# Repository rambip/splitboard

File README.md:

# Splitboard

This is the ressources we use to create our split, type matrix, bluetooth, mecanical custom keyboard.

Still in construction !

We used a lot of different technologies (solidworks for example), so you probably will not be able to recreate exactly the same keyboard.

But we added ressources you can use if you want to make your own !

## Description

pcb + 3d-printed box + aluminium plate + brown switches + adafruit feather 32u4

### Design goals:

- comfortable
	Ergonomics was the first goal of this model.
	Even if we had to make tradeoffs, the first choices (2 parts, mechanical switches, design of a new layout) were made to increase comfort.

- portable
	It is a tiny keyboard: 46 keys, measure less than 24x12 cm
	Every key has to be reachable without moving your hands at all !

- robust
	I didn't broke it yet !

- usb and bluetooth
        You can use it with any computer (mac or pc) and any modern smartphone

Our keyboard supports usb and bluetooth (BLE) communication with the *hid* specification.

## Content:

 - board design, with all components (kicad and gerber files) → `pcb`
 - ready to print STL files → `printing`
 - 3d modeling of the entire keyboard (solidworks and .step) → `3d`
 - arduino code for card → `code`

## 3d structure:

- box

- pcb

- plate

- switches

We chose the [cherry mx brown](https://www.cherrymx.de/en/mx-original/mx-brown.html).

> Pro tip: Before buying, try to find a second-hand broken keyboard somewhere !

## PCB and electronics:

We used the [adafruit 32u4](https://learn.adafruit.com/adafruit-feather-32u4-bluefruit-le/overview).

Go check out their [github account](https://github.com/adafruit), they have a lot of cool stuff !

## Software:

### Arduino

you can test our sketches if you have a 32u4 adafruit feather.

linux with arduino-cli:

First, make sure you are part of the `uucp` group.
If not, use the command `gpasswd -a $USER uucp`

`arduino-cli core install adafruit:avr`

find the board connected to usb (look at the *Port* path):
`arduino-cli board list` 

`arduino-cli board attach adafruit:avr:feather32u4`
`arduino-cli compile`
`arduino-cli upload`

### Ressources:
https://wiki.osdev.org/USB_Human_Interface_Devices

## TODO:

- [ ] convert all 3d modeling to .step
- [ ] add links to documentation

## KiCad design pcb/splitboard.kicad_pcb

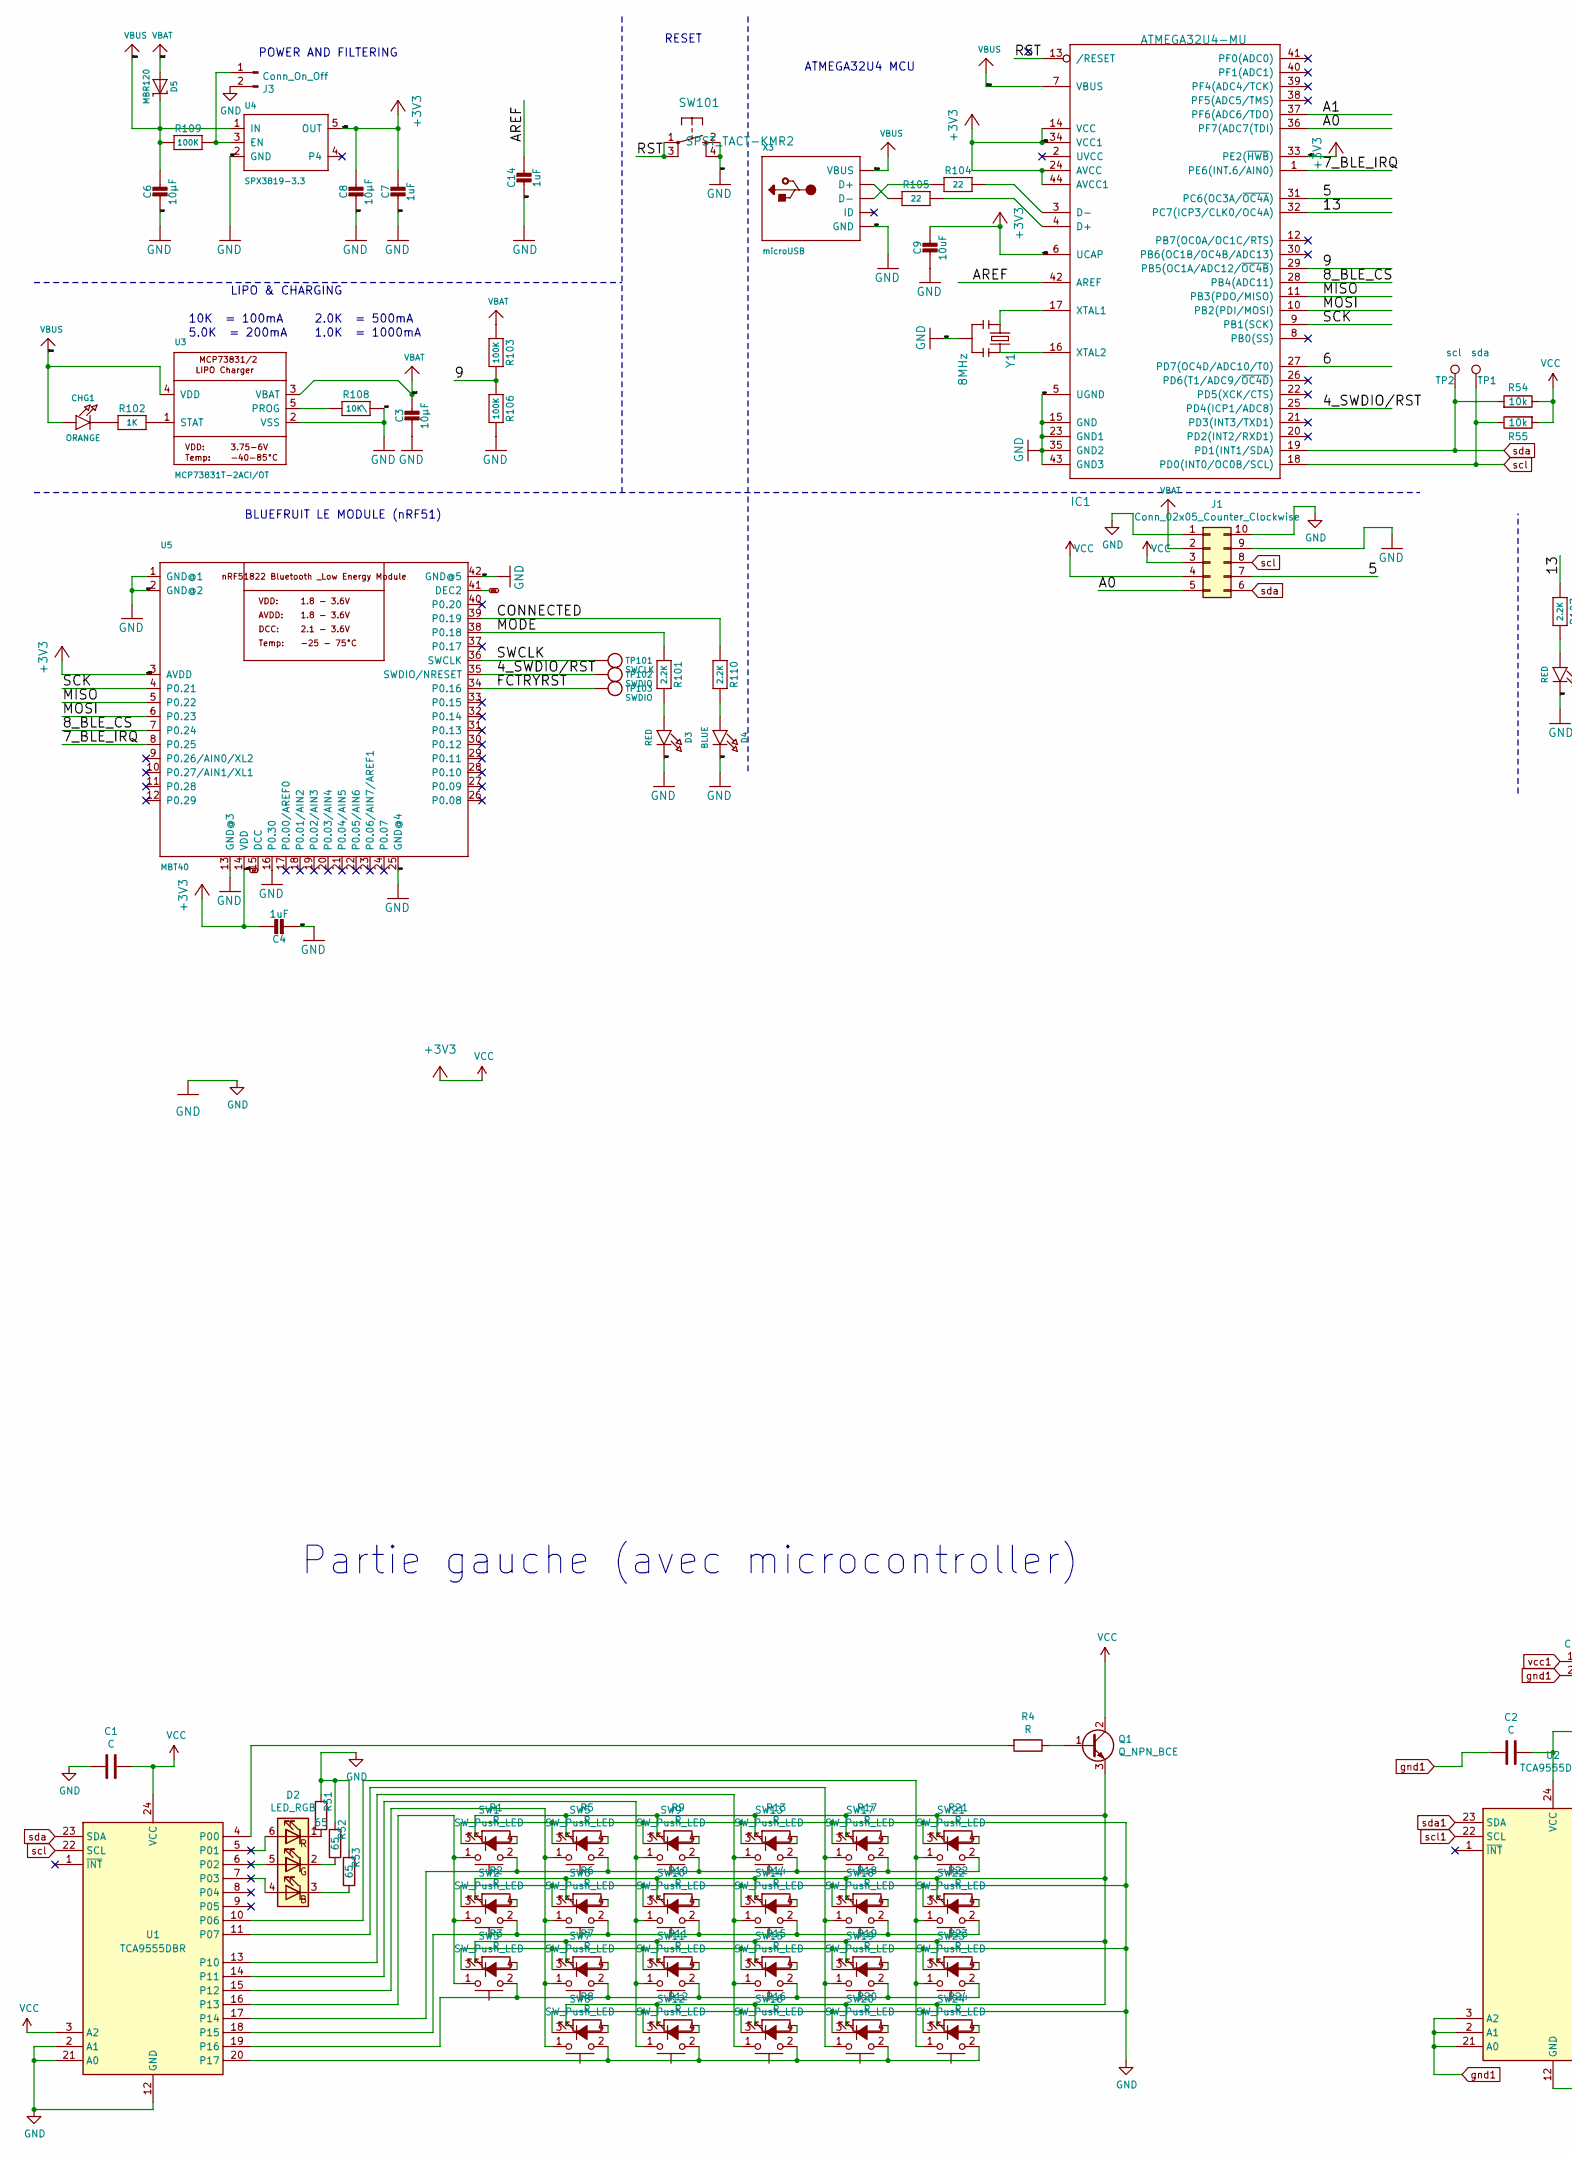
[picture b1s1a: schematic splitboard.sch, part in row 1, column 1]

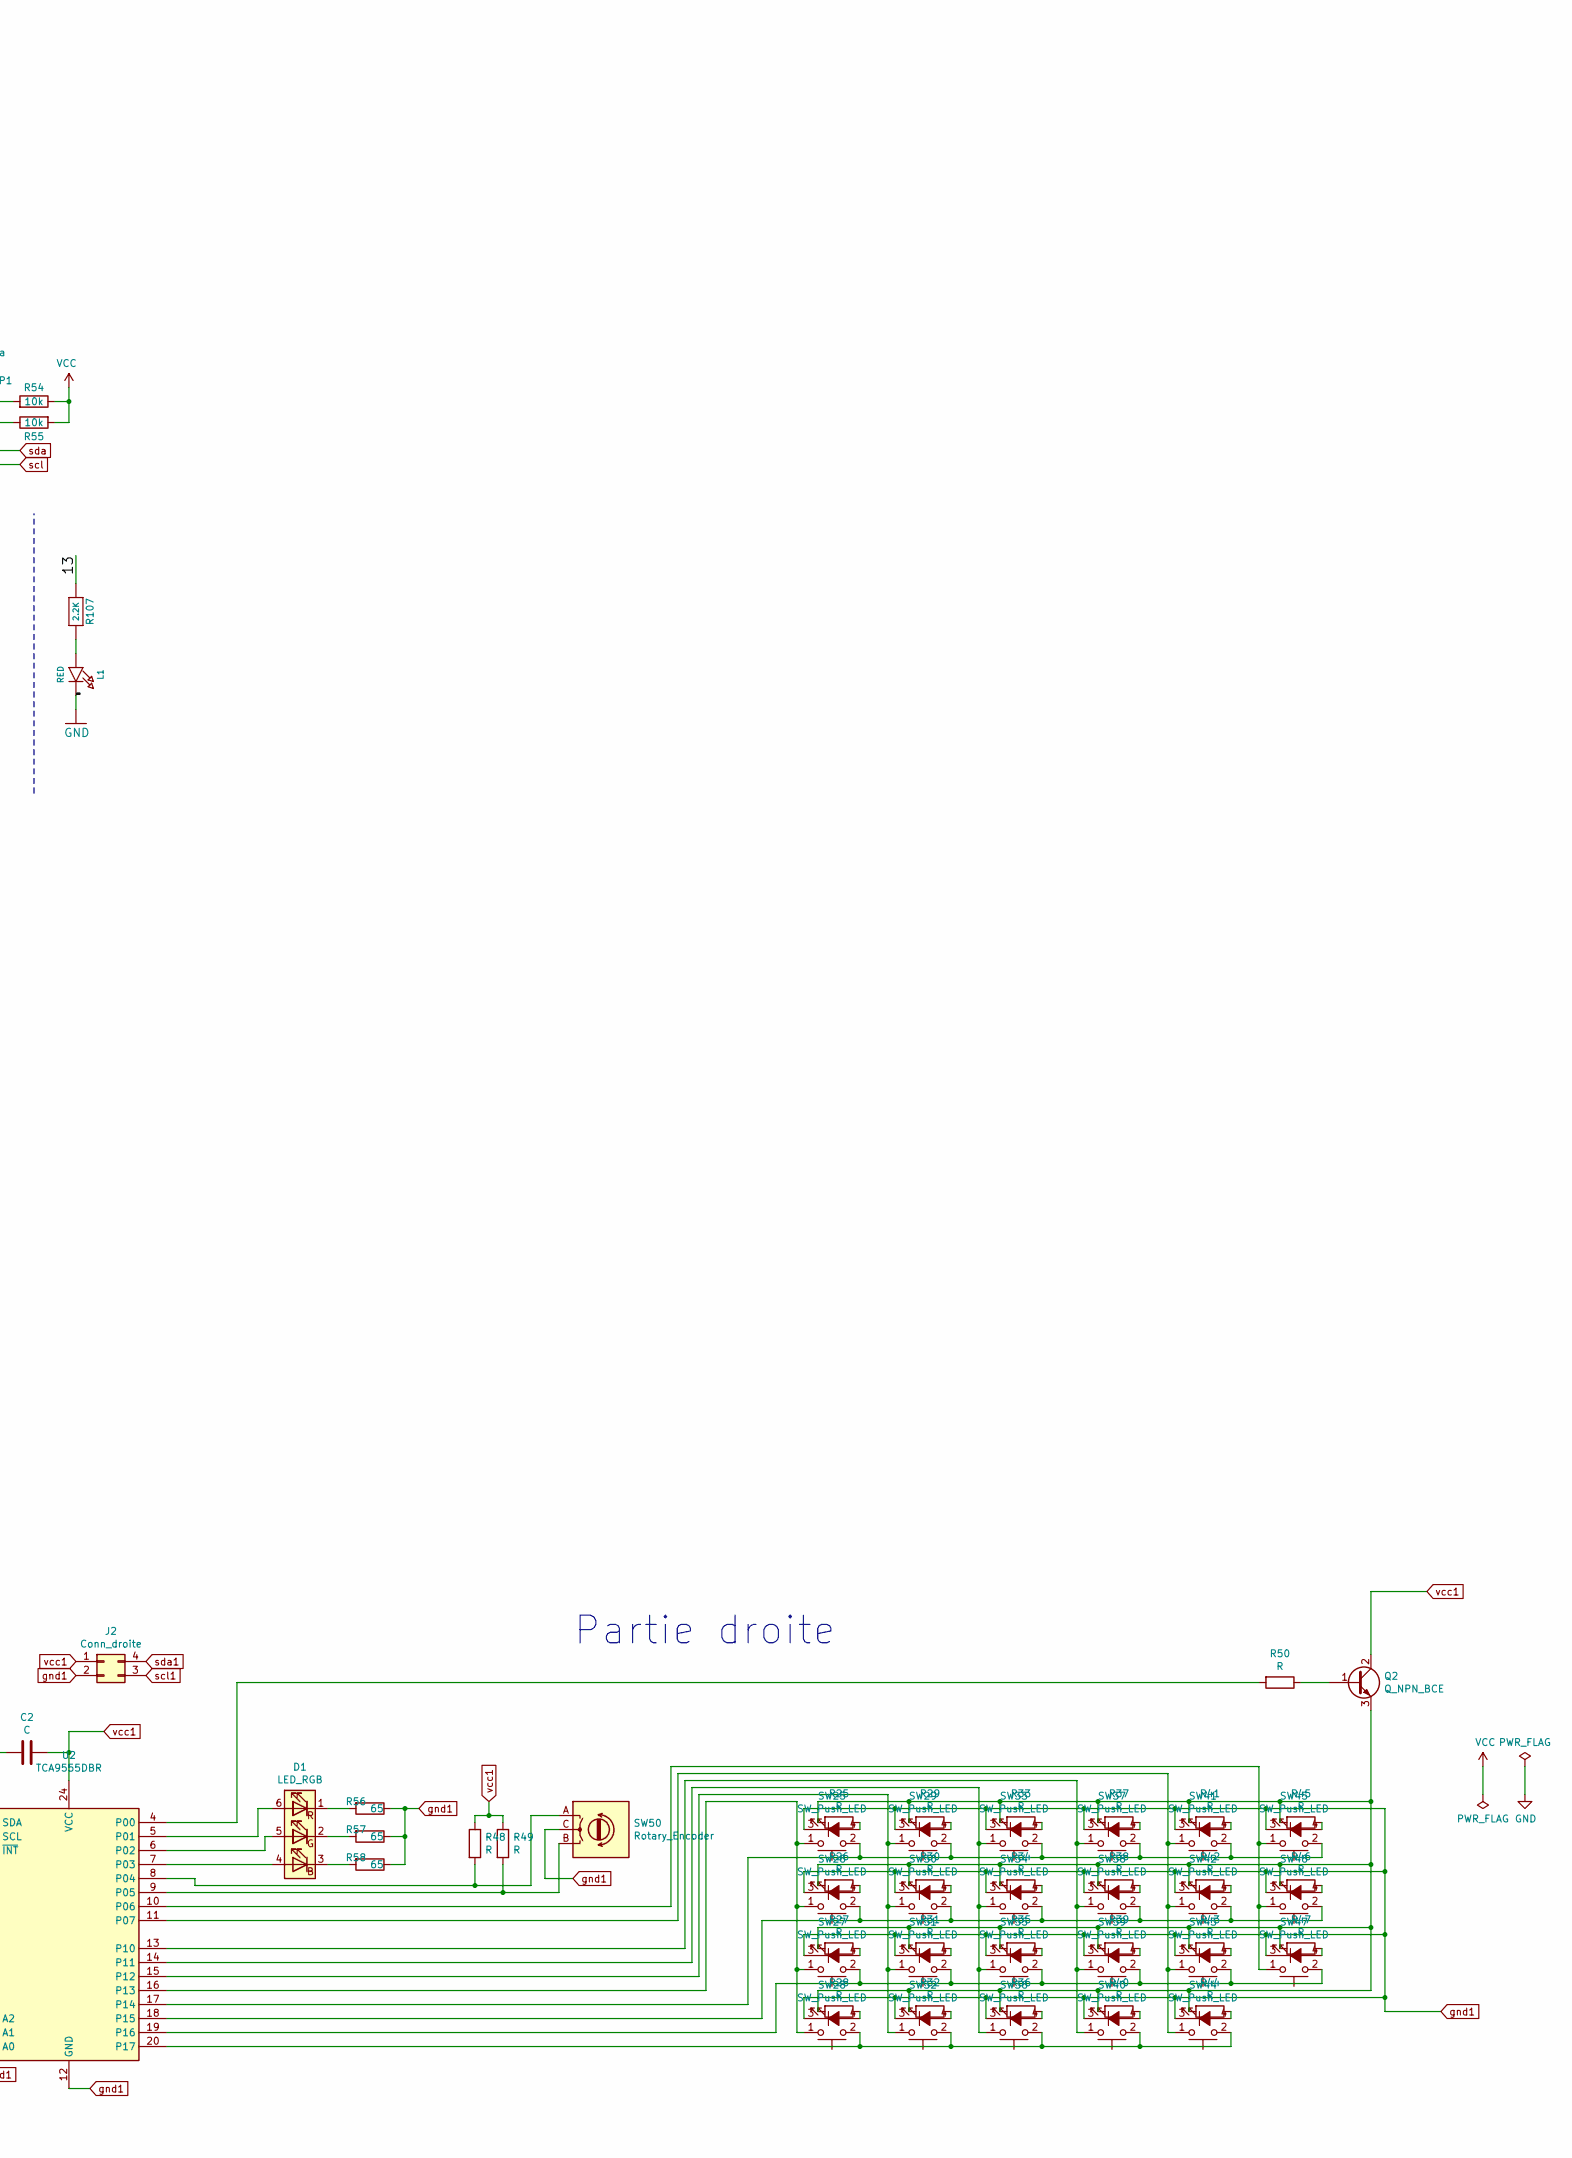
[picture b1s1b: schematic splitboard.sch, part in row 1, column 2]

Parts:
C1, C2: C; C_0603_HandSoldering
C3, C6, C8: 10µF; 0805-NO
C4, C7, C14: 1uF; 0603-NO
C9: 10uF; _0805MP
CHG1: ORANGE; CHIPLED_0805_NOOUTLINE
D1, D2: LED_RGB; LED_WS2812_PLCC6_5.0x5.0mm_P1.6mm
D3: RED; CHIPLED_0805_NOOUTLINE
D4: BLUE; CHIPLED_0805_NOOUTLINE
D5: MBR120; SOD-123
IC1: ATMEGA32U4-MU; TQFN44_7MM
J1: Conn_02x05_Counter_Clockwise; Pin_Header_Straight_2x05_Pitch2.54mm
J2: Conn_droite; PinHeader_2x02_P2.54mm_Vertical
J3: Conn_On_Off; PinHeader_1x02_P2.54mm_Vertical
L1: RED; CHIPLED_0805_NOOUTLINE
Q1, Q2: Q_NPN_BCE; SOT-23
R1, R2, R3, R4, R5, R6, R7, R8, R9, R10, R11, R12, R13, R14, R15, R16, R17, R18, R19, R20, R21, R22, R23, R24, R25, R26, R27, R28, R29, R30, R31, R32, R33, R34, R35, R36, R37, R38, R39, R40, R41, R42, R43, R44, R45, R46, R47, R48, R49, R50: R; R_0603_HandSoldering
R51, R52, R53: 65; R_0201_0603Metric_Pad0.64x0.40mm_HandSolder
R54, R55: 10k; R_0603_HandSoldering
R56, R57, R58: 65; R_0603_HandSoldering
R101, R107, R110: 2.2K; 0603-NO
R102: 1K; 0603-NO
R103, R106, R109: 100K; 0603-NO
R104, R105: 22; 0603-NO
R108: 10K\\; 0603-NO
SW1, SW2, SW3, SW5, SW6, SW7, SW8, SW9, SW10, SW11, SW12, SW13, SW14, SW15, SW16, SW17, SW18, SW19, SW20, SW21, SW22, SW23, SW24, SW25, SW26, SW27, SW28, SW29, SW30, SW31, SW32, SW33, SW34, SW35, SW36, SW37, SW38, SW39, SW40, SW41, SW42, SW43, SW44, SW45, SW46, SW47: SW_Push_LED; SW_Cherry_MX_1.00u_Plate_led
SW50: Rotary_Encoder; RotaryEncoder_Alps_EC12E_Vertical_H20mm
SW101: SPST_TACT-KMR2; KMR2
TP1: sda; TestPoint_Pad_D1.0mm
TP2: scl; TestPoint_Pad_D1.0mm
TP101: SWCLK; PAD-1.5X2.0
TP102, TP103: SWDIO; PAD-1.5X2.0
U1, U2: TCA9555DBR; SSOP-24_5.3x8.2mm_P0.65mm
U3: MCP73831T-2ACI/OT; SOT23-5
U4: SPX3819-3.3; SOT23-5
U5: MBT40; BLE_MODULE_RAYTAC_MDBT40
X3: microUSB; 4UCONN_20329_V2
Y1: 8MHz; RESONATOR-SMD

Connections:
+3V3: C1.1, C4.1, C7.1, C8.1, C9.1, IC1.6 (UCAP), IC1.14 (VCC), IC1.24 (AVCC), IC1.33 (PE2(~HWB)), IC1.34 (VCC1), IC1.44 (AVCC1), J1.3, J1.4, Q1.2 (C), R54.1, R55.2, U1.3 (A2), U1.24 (VCC), U4.5 (OUT), U5.3 (AVDD), U5.14 (VDD)
/4_SWDIO/RST: IC1.25 (PD4(ICP1/ADC8)), TP102.P$1, U5.35 (SWDIO/NRESET)
/5: IC1.31 (PC6(OC3A/~OC4A)), J1.7
/6: IC1.27 (PD7(OC4D/ADC10/T0))
/7_BLE_IRQ: IC1.1 (PE6(INT.6/AIN0)), U5.8 (P0.25)
/8_BLE_CS: IC1.28 (PB4(ADC11)), U5.7 (P0.24)
/9: IC1.29 (PB5(OC1A/ADC12/~OC4B)), R103.2, R106.1
/13: IC1.32 (PC7(ICP3/CLK0/OC4A)), R107.1
/A0: IC1.36 (PF7(ADC7(TDI)), J1.5
/A1: IC1.37 (PF6(ADC6/TDO))
/AREF: C14.1, IC1.42 (AREF)
/CONNECTED: R110.1, U5.39 (P0.19)
/FCTRYRST: TP103.P$1, U5.34 (P0.16)
/MISO: IC1.11 (PB3(PDO/MISO)), U5.5 (P0.22)
/MODE: R101.1, U5.38 (P0.18)
/MOSI: IC1.10 (PB2(PDI/MOSI)), U5.6 (P0.23)
/RST: IC1.13 (/RESET), SW101.1, SW101.3 (P1)
/SCK: IC1.9 (PB1(SCK)), U5.4 (P0.21)
/SWCLK: TP101.P$1, U5.36 (SWCLK)
DCC: U5.15 (DCC)
DEC2: U5.41 (DEC2)
GND: C1.2, C3.2, C4.2, C6.2, C7.2, C8.2, C9.2, C14.2, D3.C, D4.C, IC1.5 (UGND), IC1.15 (GND), IC1.23 (GND1), IC1.35 (GND2), IC1.43 (GND3), J1.1, J1.9, J1.10, J3.2, L1.C, R51.2, R52.2, R53.2, R106.2, R108.2, SW1.3 (K), SW2.3 (K), SW3.3 (K), SW5.3 (K), SW6.3 (K), SW7.3 (K), SW8.3 (K), SW9.3 (K), SW10.3 (K), SW11.3 (K), SW12.3 (K), SW13.3 (K), SW14.3 (K), SW15.3 (K), SW16.3 (K), SW17.3 (K), SW18.3 (K), SW19.3 (K), SW20.3 (K), SW21.3 (K), SW22.3 (K), SW23.3 (K), SW24.3 (K), SW101.2 (S), SW101.4 (S1), U1.2 (A1), U1.12 (GND), U1.21 (A0), U3.2 (VSS), U4.2 (GND), U5.1 (GND@1), U5.2 (GND@2), U5.13 (GND@3), U5.16 (P0.30), U5.25 (GND@4), U5.42 (GND@5), X3.BASE@1 (GND), X3.BASE@2 (GND), X3.GND, X3.SPRT@1 (GND), X3.SPRT@2 (GND), X3.SPRT@3 (GND), X3.SPRT@4 (GND), Y1.2
unnamed: CHG1.C, R102.1
unnamed: D1.1 (RK), R56.2
unnamed: D1.2 (GK), R57.2
unnamed: D1.3 (BK), R58.2
unnamed: D1.4 (BA), U2.7 (P03)
unnamed: D1.5 (GA), U2.6 (P02)
unnamed: D1.6 (RA), U2.5 (P01)
unnamed: D2.1 (RK), R51.1
unnamed: D2.2 (GK), R52.1
unnamed: D2.3 (BK), R53.1
unnamed: D2.4 (BA), U1.7 (P03)
unnamed: D2.5 (GA), U1.6 (P02)
unnamed: D2.6 (RA), U1.5 (P01)
unnamed: D3.A, R101.2
unnamed: D4.A, R110.2
unnamed: IC1.3 (D-), R104.2
unnamed: IC1.4 (D+), R105.2
unnamed: IC1.16 (XTAL2), Y1.3
unnamed: IC1.17 (XTAL1), Y1.1
unnamed: J3.1, R109.2, U4.3 (EN)
unnamed: L1.A, R107.2
unnamed: Q1.1 (B), R4.1
unnamed: Q1.3 (E), R1.2, R2.2, R3.2, R5.2, R6.2, R7.2, R8.2, R9.2, R10.2, R11.2, R12.2, R13.2, R14.2, R15.2, R16.2, R17.2, R18.2, R19.2, R20.2, R21.2, R22.2, R23.2, R24.2
unnamed: Q2.1 (B), R50.1
unnamed: Q2.3 (E), R25.2, R26.2, R27.2, R28.2, R29.2, R30.2, R31.2, R32.2, R33.2, R34.2, R35.2, R36.2, R37.2, R38.2, R39.2, R40.2, R41.2, R42.2, R43.2, R44.2, R45.2, R46.2, R47.2
unnamed: R1.1, SW1.4 (A)
unnamed: R2.1, SW2.4 (A)
unnamed: R3.1, SW3.4 (A)
unnamed: R4.2, U1.4 (P00)
unnamed: R5.1, SW5.4 (A)
unnamed: R6.1, SW6.4 (A)
unnamed: R7.1, SW7.4 (A)
unnamed: R8.1, SW8.4 (A)
unnamed: R9.1, SW9.4 (A)
unnamed: R10.1, SW10.4 (A)
unnamed: R11.1, SW11.4 (A)
unnamed: R12.1, SW12.4 (A)
unnamed: R13.1, SW13.4 (A)
unnamed: R14.1, SW14.4 (A)
unnamed: R15.1, SW15.4 (A)
unnamed: R16.1, SW16.4 (A)
unnamed: R17.1, SW17.4 (A)
unnamed: R18.1, SW18.4 (A)
unnamed: R19.1, SW19.4 (A)
unnamed: R20.1, SW20.4 (A)
unnamed: R21.1, SW21.4 (A)
unnamed: R22.1, SW22.4 (A)
unnamed: R23.1, SW23.4 (A)
unnamed: R24.1, SW24.4 (A)
unnamed: R25.1, SW25.4 (A)
unnamed: R26.1, SW26.4 (A)
unnamed: R27.1, SW27.4 (A)
unnamed: R28.1, SW28.4 (A)
unnamed: R29.1, SW29.4 (A)
unnamed: R30.1, SW30.4 (A)
unnamed: R31.1, SW31.4 (A)
unnamed: R32.1, SW32.4 (A)
unnamed: R33.1, SW33.4 (A)
unnamed: R34.1, SW34.4 (A)
unnamed: R35.1, SW35.4 (A)
unnamed: R36.1, SW36.4 (A)
unnamed: R37.1, SW37.4 (A)
unnamed: R38.1, SW38.4 (A)
unnamed: R39.1, SW39.4 (A)
unnamed: R40.1, SW40.4 (A)
unnamed: R41.1, SW41.4 (A)
unnamed: R42.1, SW42.4 (A)
unnamed: R43.1, SW43.4 (A)
unnamed: R44.1, SW44.4 (A)
unnamed: R45.1, SW45.4 (A)
unnamed: R46.1, SW46.4 (A)
unnamed: R47.1, SW47.4 (A)
unnamed: R48.2, SW50.A, U2.8 (P04)
unnamed: R49.2, SW50.B, U2.9 (P05)
unnamed: R50.2, U2.4 (P00)
unnamed: R102.2, U3.1 (STAT)
unnamed: R104.1, X3.D-
unnamed: R105.1, X3.D+
unnamed: R108.1, U3.5 (PROG)
unnamed: SW1.1, SW2.1, SW3.1, U1.16 (P13)
unnamed: SW1.2, SW5.2, SW9.2, SW13.2, SW17.2, SW21.2, U1.17 (P14)
unnamed: SW5.1, SW6.1, SW7.1, SW8.1, U1.15 (P12)
unnamed: SW9.1, SW10.1, SW11.1, SW12.1, U1.14 (P11)
unnamed: SW2.2, SW6.2, SW10.2, SW14.2, SW18.2, SW22.2, U1.18 (P15)
unnamed: SW3.2, SW7.2, SW11.2, SW15.2, SW19.2, SW23.2, U1.19 (P16)
unnamed: SW8.2, SW12.2, SW16.2, SW20.2, SW24.2, U1.20 (P17)
unnamed: SW13.1, SW14.1, SW15.1, SW16.1, U1.13 (P10)
unnamed: SW17.1, SW18.1, SW19.1, SW20.1, U1.11 (P07)
unnamed: SW21.1, SW22.1, SW23.1, SW24.1, U1.10 (P06)
unnamed: SW25.1, SW26.1, SW27.1, SW28.1, U2.16 (P13)
unnamed: SW25.2, SW29.2, SW33.2, SW37.2, SW41.2, SW45.2, U2.17 (P14)
unnamed: SW26.2, SW30.2, SW34.2, SW38.2, SW42.2, SW46.2, U2.18 (P15)
unnamed: SW27.2, SW31.2, SW35.2, SW39.2, SW43.2, SW47.2, U2.19 (P16)
unnamed: SW28.2, SW32.2, SW36.2, SW40.2, SW44.2, U2.20 (P17)
unnamed: SW29.1, SW30.1, SW31.1, SW32.1, U2.15 (P12)
unnamed: SW33.1, SW34.1, SW35.1, SW36.1, U2.14 (P11)
unnamed: SW37.1, SW38.1, SW39.1, SW40.1, U2.13 (P10)
unnamed: SW41.1, SW42.1, SW43.1, SW44.1, U2.11 (P07)
unnamed: SW45.1, SW46.1, SW47.1, U2.10 (P06)
VBAT: C3.1, D5.A, J1.2, R103.1, U3.3 (VBAT)
VBUS: C6.1, CHG1.A, D5.C, IC1.7 (VBUS), R109.1, U3.4 (VDD), U4.1 (IN), X3.VBUS
gnd1: C2.2, J2.2, R56.1, R57.1, R58.1, SW25.3 (K), SW26.3 (K), SW27.3 (K), SW28.3 (K), SW29.3 (K), SW30.3 (K), SW31.3 (K), SW32.3 (K), SW33.3 (K), SW34.3 (K), SW35.3 (K), SW36.3 (K), SW37.3 (K), SW38.3 (K), SW39.3 (K), SW40.3 (K), SW41.3 (K), SW42.3 (K), SW43.3 (K), SW44.3 (K), SW45.3 (K), SW46.3 (K), SW47.3 (K), SW50.C, U2.2 (A1), U2.3 (A2), U2.12 (GND), U2.21 (A0)
scl: IC1.18 (PD0(INT0/OC0B/SCL)), J1.8, R55.1, TP1.1, U1.22 (SCL)
scl1: J2.3, U2.22 (SCL)
sda: IC1.19 (PD1(INT1/SDA)), J1.6, R54.2, TP2.1, U1.23 (SDA)
sda1: J2.4, U2.23 (SDA)
vcc1: C2.1, J2.1, Q2.2 (C), R48.1, R49.1, U2.24 (VCC)

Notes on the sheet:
Partie gauche (avec microcontroller)
Partie droite
POWER AND FILTERING
BLUEFRUIT LE MODULE (nRF51)
RESET
ATMEGA32U4 MCU
10K = 100mA
5.0K = 200mA
2.0K = 500mA
1.0K = 1000mA
LIPO & CHARGING

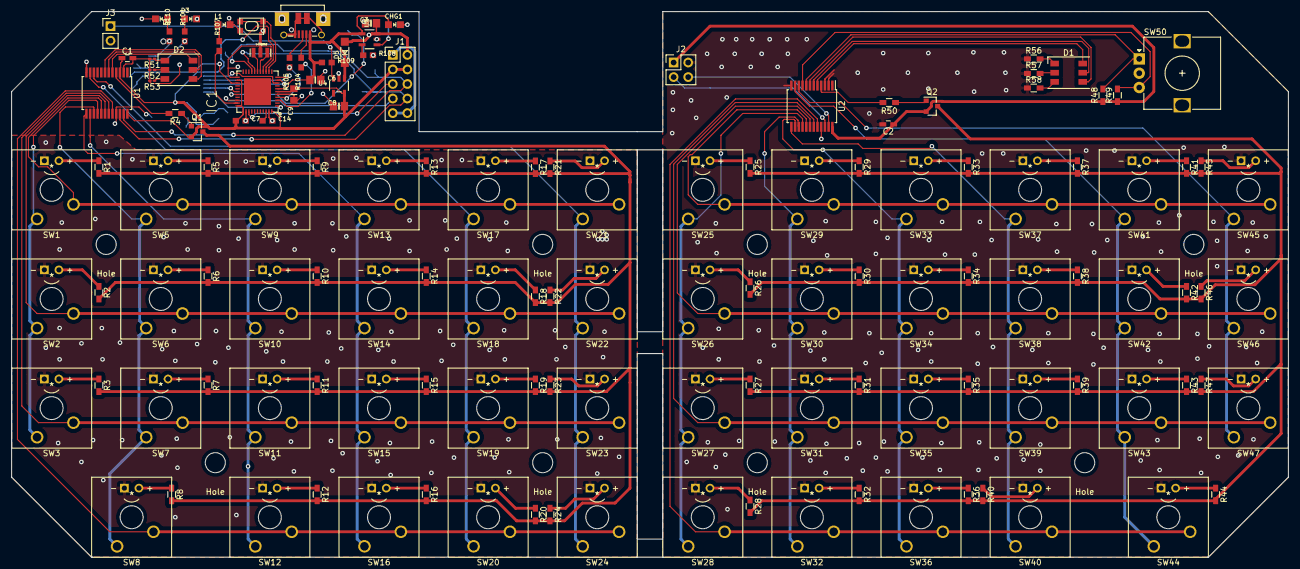
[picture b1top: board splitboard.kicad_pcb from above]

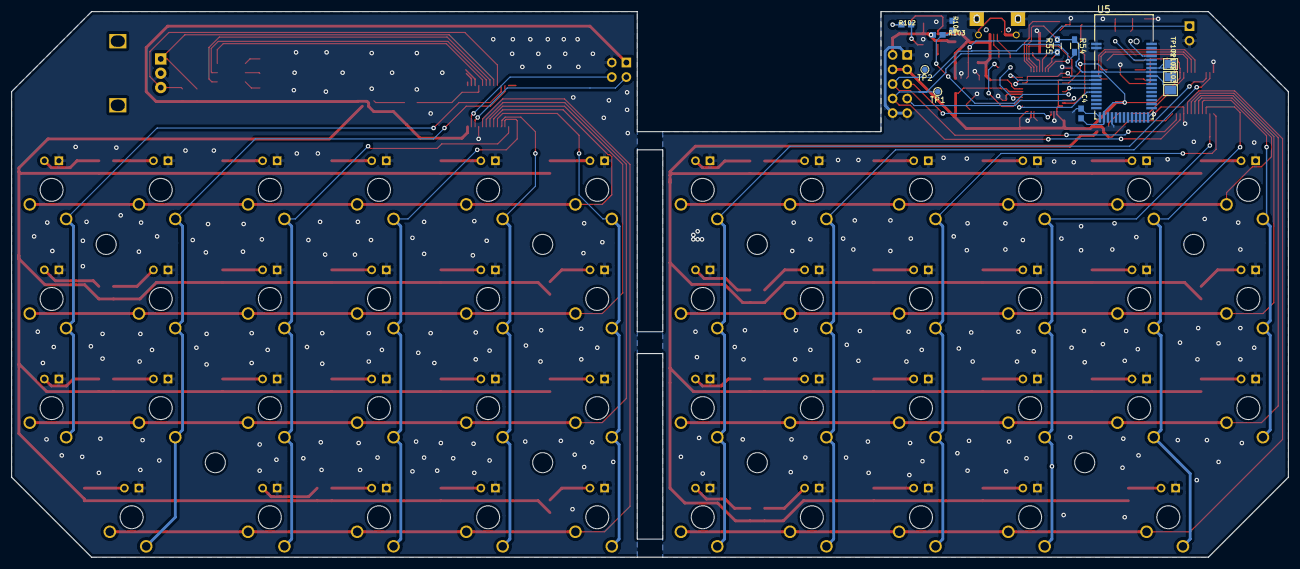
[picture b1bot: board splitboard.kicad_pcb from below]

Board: 2 copper layers, 222.9 x 95.2 mm, 158 parts (12 on the bottom side), 125 nets.

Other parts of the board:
Hole: M3; screwhole
Hole#2, Hole#3, Hole#4, Hole#5, Hole#6, Hole#7, Hole#8: M3; screwhole

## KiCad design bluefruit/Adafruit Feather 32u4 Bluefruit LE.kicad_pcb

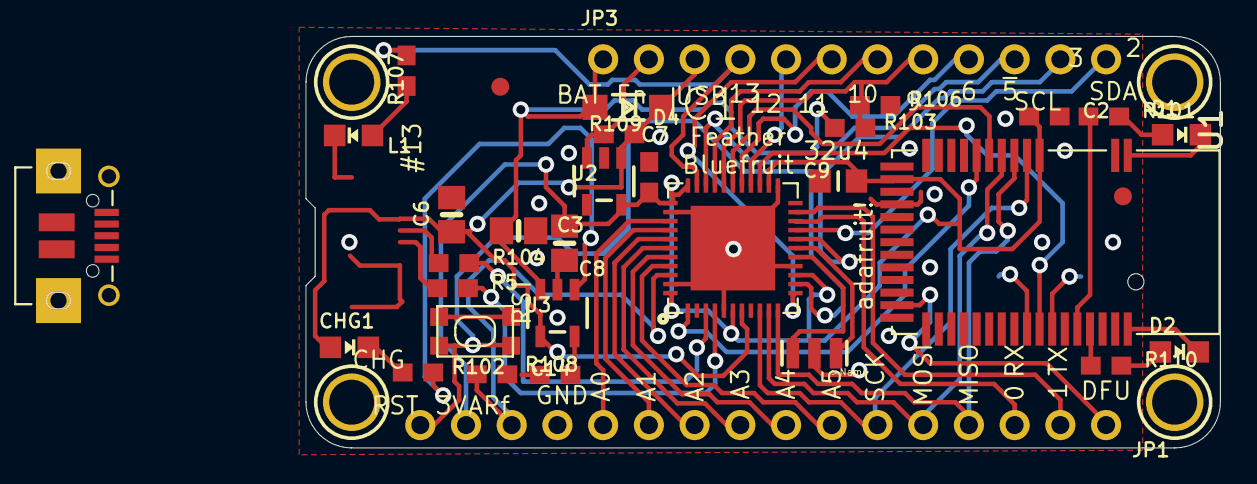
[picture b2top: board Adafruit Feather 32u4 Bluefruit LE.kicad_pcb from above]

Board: 2 copper layers, 65.2 x 22.9 mm, 40 parts (0 on the bottom side), 47 nets.

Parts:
C2, C7, C14: 1uF; 0603-NO
C3, C6, C8: 10µF; 0805-NO
C9: 10uF; _0805MP
CHG1: ORANGE; CHIPLED_0805_NOOUTLINE
D1: RED; CHIPLED_0805_NOOUTLINE
D2: BLUE; CHIPLED_0805_NOOUTLINE
D4: MBR120; SOD-123
IC1: ATMEGA32U4-MU; TQFN44_7MM
JP1: HEADER-1X16ROUND; 1X16_ROUND
JP3: HEADER-1X12; 1X12_ROUND
L1: RED; CHIPLED_0805_NOOUTLINE
R5, R104: 22; 0603-NO
R101, R107, R110: 2.2K; 0603-NO
R102: 1K; 0603-NO
R103, R106, R109: 100K; 0603-NO
R108: 10K\; 0603-NO
SW1: SPST_TACT-KMR2; KMR2
TP1: SWCLK; PAD-1.5X2.0
TP2, TP3: SWDIO; PAD-1.5X2.0
U1: MBT40; BLE_MODULE_RAYTAC_MDBT40
U2: SPX3819-3.3; SOT23-5
U3: MCP73831T-2ACI/OT; SOT23-5
U$6, U$24, U$31, U$32: MOUNTINGHOLE2.5; MOUNTINGHOLE_2.5_PLATED
U$34, U$35: FIDUCIAL; FIDUCIAL_1MM
X3: microUSB; 4UCONN_20329_V2
Y1: 8MHz; RESONATOR-SMD

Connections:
+3V3: C2.1, C7.1, C8.1, C9.1, IC1.6, IC1.14, IC1.24, IC1.33, IC1.34, IC1.44, JP1.15, U1.3, U1.14, U2.5
/0: IC1.20, JP1.3
/1: IC1.21, JP1.2
/2: IC1.19, JP3.12
/3: IC1.18, JP3.11
/4_SWDIO/RST: IC1.25, TP2.P$1, U1.35
/5: IC1.31, JP3.10
/6: IC1.27, JP3.9
/7_BLE_IRQ: IC1.1, U1.8
/8_BLE_CS: IC1.28, U1.7
/9: IC1.29, JP3.8, R103.2, R106.1
/10: IC1.30, JP3.7
/11: IC1.12, JP3.6
/12: IC1.26, JP3.5
/13: IC1.32, JP3.4, R107.1
/A0: IC1.36, JP1.12
/A1: IC1.37, JP1.11
/A2: IC1.38, JP1.10
/A3: IC1.39, JP1.9
/A4: IC1.40, JP1.8
/A5: IC1.41, JP1.7
/AREF: C14.1, IC1.42, JP1.14
/CONNECTED: R110.1, U1.39
/DFU: JP1.1, U1.24
/EN: JP3.2, R109.2, U2.3
/FCTRYRST: TP3.P$1, U1.34
/MISO: IC1.11, JP1.4, U1.5
/MODE: R101.1, U1.38
/MOSI: IC1.10, JP1.5, U1.6
/RST: IC1.13, JP1.16, SW1.1, SW1.3
/SCK: IC1.9, JP1.6, U1.4
/SWCLK: TP1.P$1, U1.36
GND: C2.2, C3.2, C6.2, C7.2, C8.2, C9.2, C14.2, D1.C, D2.C, IC1.5, IC1.15, IC1.23, IC1.35, IC1.43, JP1.13, L1.C, R106.2, R108.2, SW1.2, SW1.4, U1.1, U1.2, U1.13, U1.16, U1.25, U1.42, U2.2, U3.2, X3.BASE@1, X3.BASE@2, X3.GND, X3.SPRT@1, X3.SPRT@2, X3.SPRT@3, X3.SPRT@4, Y1.2
unnamed: CHG1.C, R102.1
unnamed: D1.A, R101.2
unnamed: D2.A, R110.2
unnamed: IC1.3, R104.2
unnamed: IC1.4, R5.2
unnamed: IC1.16, Y1.3
unnamed: IC1.17, Y1.1
unnamed: L1.A, R107.2
unnamed: R5.1, X3.D+
unnamed: R102.2, U3.1
unnamed: R104.1, X3.D-
unnamed: R108.1, U3.5
VBAT: C3.1, D4.A, JP3.1, R103.1, U3.3
VBUS: C6.1, CHG1.A, D4.C, IC1.7, JP3.3, R109.1, U2.1, U3.4, X3.VBUS

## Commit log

2021-04-21 renamed folder and changed pcb
2021-04-21 fixed syntax error
2021-04-21 content
2021-04-21 added 3d models
2021-04-21 added measures in pcb
2021-04-23 added code
2021-04-23 readme
2021-04-24 exported pcb to step/solidworks
2021-04-24 added image
2021-04-24 changed readme
2021-04-24 plan de masse gauche
2021-04-24 original feather 32u4 pcb
2021-04-24 fixed feather shematics
2021-04-24 changed dimensions
2021-04-25 plan de masse droite
2021-04-25 added .step of 3d model
2021-04-25 check wires
2021-04-29 check wires and gnd
2021-04-29 added hole for screws in kicad
2021-04-29 updated pcb and holes
2021-04-29 updated pretty image
2021-04-30 changed hole dimensions
2021-04-30 holes, dimensions and screws
2021-04-30 holes dimensions
2021-04-30 added screws, spacers and nuts
2021-04-30 better image
2021-05-01 gerber
2021-05-01 pcb origin
2021-05-01 pcb via
2021-05-03 drill
2021-05-22 exported for cnc
2021-05-23 exported spacer for 3D printing
2021-05-24 last revision before machining
2021-06-01 finitions for plate and 3d printed support
2021-06-01 removed useless files
2021-06-08 for printing
2021-06-09 modifications for cable
2021-06-14 new images
2021-06-18 added stl files for keycaps
2021-07-06 added usable code
2021-07-07 added useable code, with comments
2021-08-01 fixed '*' on azerty
2021-08-01 changed space bar logic
2021-08-01 more readable bitwise operation
2021-08-01 personal config
2021-08-01 ignore sketch.json
2021-08-03 restored bluetooth
2021-08-27 fixed bug with layer keys
2021-08-27 fixed same layer bug with space key
2021-09-26 renamed code tests to explain what they do
2021-09-26 added option to change keymap with rotary encoder
2021-10-02 Fixed bluetooth issue and switched azerty and qwerty
2021-10-25 created help to compile and minor keyboard change
2021-11-05 started refactoring for layout to os encoding
